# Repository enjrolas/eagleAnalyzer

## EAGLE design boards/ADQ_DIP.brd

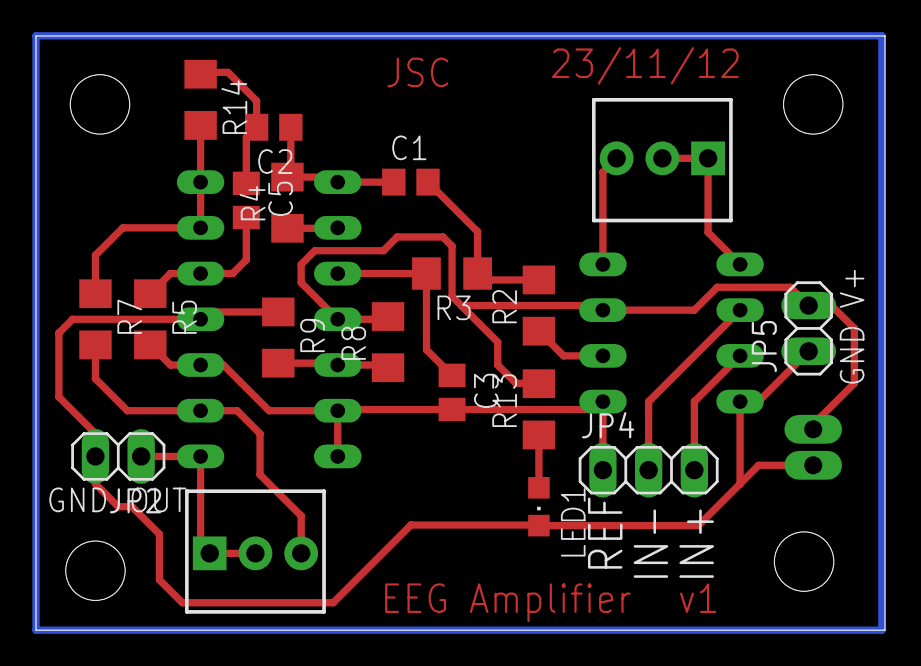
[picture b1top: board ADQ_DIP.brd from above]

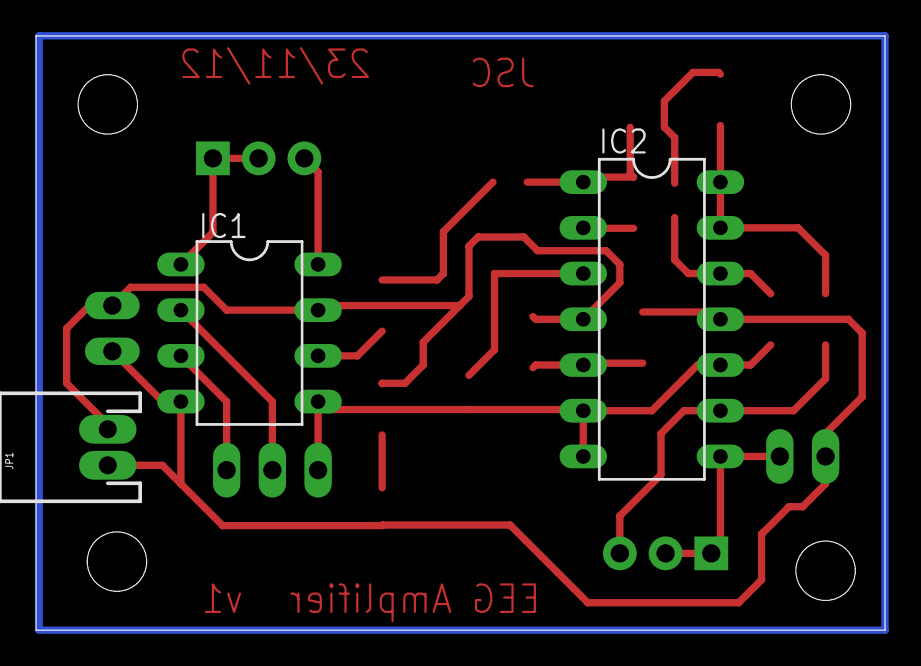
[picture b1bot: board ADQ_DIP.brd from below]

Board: 2 copper layers, 47.2 x 33.0 mm, 26 parts (3 on the bottom side), 19 nets.

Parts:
C1: 220n; C0805
C2, C5: 10u; C0805
C3: 100n; C0805
IC1: AD620N; DIL08
IC2: TL074P; DIL14
JP1: JST-2-PTH
JP2: OUTPUT; 1X02
JP3, JP6, JP7, JP8: STAND-OFF
JP4: INPUT; 1X03
JP5: V+ alt; 1X02
LED1: GREEN; CHIPLED_0805
R1: 500 OHM; 3362U-2
R2, R3: 33k; R1206
R4: 100k; R1206
R5, R8, R9: 51k; R1206
R6: 100k OHM; 3362U-2
R7, R13: 1k; R1206
R14: 22k; R1206

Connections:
GND: IC1.4, IC2.11, JP1.1, JP2.2, JP5.1, LED1.C, R9.1
IN+: IC1.3, JP4.3
IN-: IC1.2, JP4.2
unnamed: IC1.8, R1.3
unnamed: IC1.1, R1.1, R1.2
unnamed: C1.2, R2.2, R3.1
unnamed: IC1.6, R2.1
unnamed: C3.1, IC2.3, R3.2
unnamed: IC2.2, R4.1
unnamed: C1.1, C2.1, IC2.1, R4.2
unnamed: LED1.A, R13.1
unnamed: C2.2, C5.1, R14.1
unnamed: IC2.13, IC2.14, R7.1, R14.2
unnamed: IC2.5, R8.1, R9.2
unnamed: IC2.9, R6.3, R7.2
unnamed: C5.2, IC2.12, R5.1
OUT: IC2.8, JP2.1, R6.1, R6.2
VCC: IC1.7, IC2.4, JP1.2, JP5.2, R8.2, R13.2
VCC/2: C3.2, IC1.5, IC2.6, IC2.7, IC2.10, JP4.1, R5.2

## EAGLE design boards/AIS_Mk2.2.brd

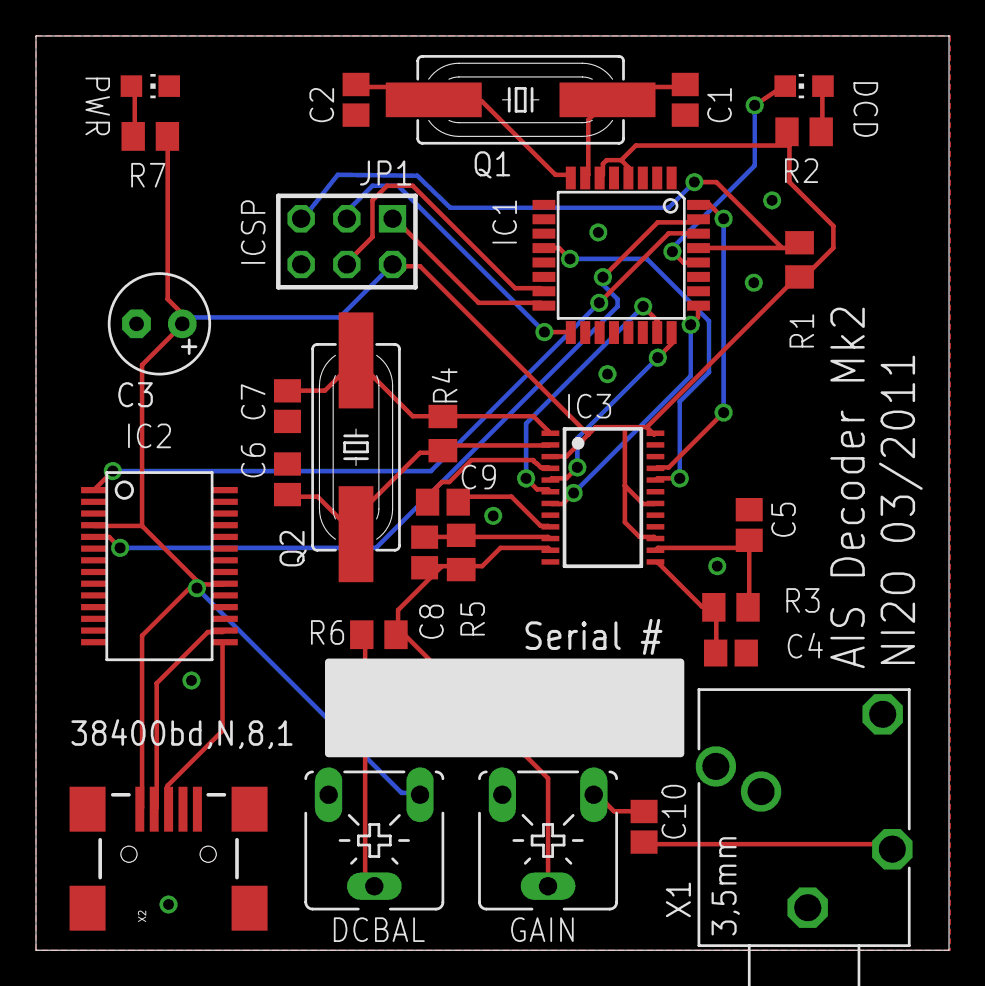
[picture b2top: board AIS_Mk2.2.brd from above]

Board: 2 copper layers, 50.7 x 50.8 mm, 29 parts (0 on the bottom side), 30 nets.

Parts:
C1, C2: 33pF; C0805
C3: 1uF; E2,5-6
C4, C5: 15nF; C0805
C6, C7, C8: 22pF; C0805
C9, C10: 10nF; C0805
DCBAL: 100K; CA6V
GAIN: 100K; CA6V
IC1: MEGA8-AI; TQFP32-08
IC2: FT232RL-BASICSSOP; SSOP28DB
IC3: CMX589AE2; TSSOP24
JP1: AVR-ISP-6
LED1: DATA; CHIP-LED0805
LED2: PWR; CHIP-LED0805
Q1: 8MHz; HC49UP
Q2: 4.9152MHz; HC49UP
R1: 10K; M0805
R2: 470R; M0805
R3, R4: 1M; M0805
R5: 100K; M0805
R6: 270K; M0805
R7: 1K; M0805
X1: PG203J
X2: USBSMD; USB-MINIB

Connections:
+5V: C3.+, DCBAL.A, IC1.4, IC1.6, IC2.4, IC2.20, IC3.3, IC3.15, IC3.18, IC3.24, JP1.2, R1.2, R2.2, R7.1, X2.VBUS
DCBAL: DCBAL.S, R6.1
GND: C1.2, C2.2, C3.-, C4.2, C5.2, C6.2, C7.2, C9.2, DCBAL.E, IC1.3, IC1.5, IC1.21, IC2.7, IC2.18, IC2.21, IC2.25, IC2.26, IC3.4, IC3.8, IC3.12, IC3.17, JP1.6, LED2.C, X1.1, X1.2, X1.3, X2.GND
unnamed: C2.1, IC1.8, Q1.1
unnamed: C1.1, IC1.7, Q1.2
unnamed: IC1.17, JP1.3
unnamed: IC1.16, JP1.1
unnamed: IC1.29, JP1.5, R1.1
unnamed: C4.1, IC3.13, R3.1
unnamed: IC1.28, LED1.C
unnamed: LED1.A, R2.1
unnamed: C5.1, IC3.14, R3.2
unnamed: IC1.30, IC2.1
unnamed: IC1.31, IC2.5
unnamed: C7.1, IC3.1, Q2.1, R4.1
unnamed: C6.1, IC3.2, Q2.2, R4.2
unnamed: C8.1, IC3.10, R5.2
unnamed: C10.2, GAIN.A
unnamed: C10.1, X1.5
unnamed: C9.1, IC3.9
unnamed: IC1.32, IC3.21
unnamed: IC1.12, IC3.20
unnamed: IC1.24, IC3.5
unnamed: IC1.23, IC3.6
unnamed: IC1.25, IC3.7
unnamed: LED2.A, R7.2
unnamed: IC1.15, JP1.4
SIG: C8.2, GAIN.S, IC3.11, R5.1, R6.2
USB+: IC2.15, X2.D+
USB-: IC2.16, X2.D-

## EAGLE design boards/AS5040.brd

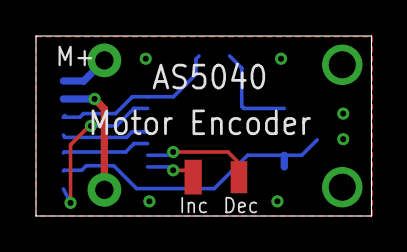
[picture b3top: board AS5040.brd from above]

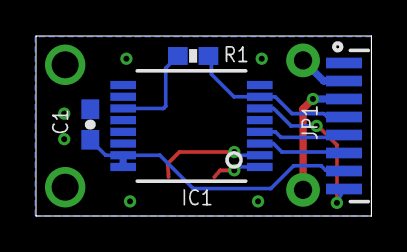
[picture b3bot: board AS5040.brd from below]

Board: 2 copper layers, 18.6 x 10.0 mm, 7 parts (4 on the bottom side), 10 nets.

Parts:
C1: 0603-CAP
IC1: AS5040; SSOP16
JP1: BM08B
JP2: 1X2SMD
JP3, JP5: M01SMDNS; 1X01NS
R1: 0603-RES

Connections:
3.3V: C1.1, IC1.15, IC1.16, JP1.7
CHA: IC1.3, JP1.6
CHB: IC1.4, JP1.5
GND: C1.2, IC1.7, JP1.4, R1.1
INDEX: IC1.6, JP1.8
M1: JP1.3, JP3.1
M2: JP1.2, JP5.1
unnamed: IC1.11, R1.2
unnamed: IC1.1, JP2.P$2
unnamed: IC1.2, JP2.P$1

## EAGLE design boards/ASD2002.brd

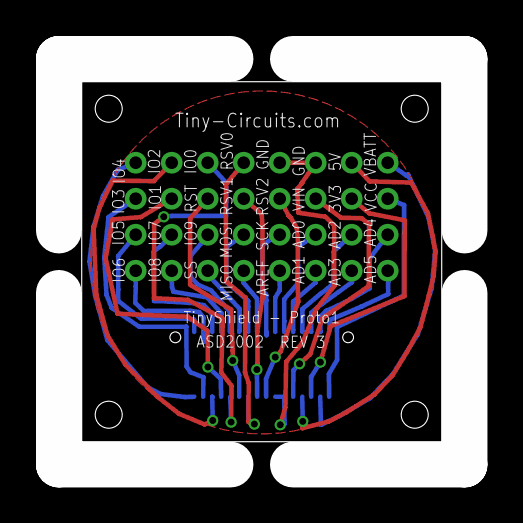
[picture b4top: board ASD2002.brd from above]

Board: 2 copper layers, 20.0 x 20.0 mm, 34 parts (1 on the bottom side), 31 nets.

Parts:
J1: DF12-32-DS
J2, J3, J4, J5, J6, J7, J8, J9, J10, J11, J12, J13, J14, J15, J16, J17, J18, J19, J20, J21, J22, J23, J24, J25, J26, J27, J28, J29, J30, J31, J32, J33: PIN_1X.1"; 1X.1"
U$1: DOCFIELD-TINYCIRCUITS-PCB

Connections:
+3V3: J1.6, J4.1
+5V: J1.8, J5.1
AD0: J1.11, J15.1
AD1: J1.9, J14.1
AD2: J1.7, J13.1
AD3: J1.5, J12.1
AD4/SDA: J1.3, J11.1
AD5/SCL: J1.1, J10.1
AREF: J1.13, J16.1
GND: J1.12, J1.14, J9.1, J33.1
IO0: J1.24, J30.1
IO1: J1.26, J29.1
IO2: J1.28, J28.1
IO3: J1.30, J27.1
IO4: J1.32, J26.1
IO5: J1.31, J25.1
IO6: J1.29, J24.1
IO7: J1.27, J23.1
IO8: J1.25, J22.1
IO9: J1.23, J21.1
MISO: J1.17, J18.1
MOSI: J1.19, J19.1
RESET: J1.22, J31.1
RSV0: J1.20, J17.1
RSV1: J1.18, J8.1
RSV2: J1.16, J7.1
SCK: J1.15, J32.1
SS: J1.21, J20.1
VBATT: J1.4, J3.1
VCC: J1.2, J2.1
VIN: J1.10, J6.1

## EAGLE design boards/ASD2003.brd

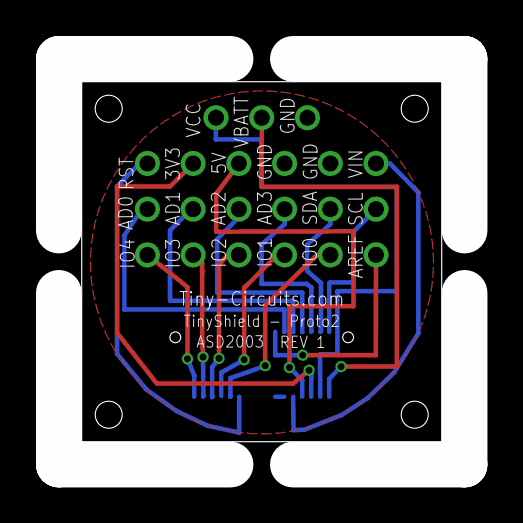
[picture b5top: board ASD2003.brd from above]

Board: 2 copper layers, 20.0 x 20.0 mm, 23 parts (1 on the bottom side), 19 nets.

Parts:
J1, J2, J3, J4, J5, J6, J7, J8, J9, J10, J11, J13, J14, J15, J16, J17, J18, J19, J20, J21, J22: PIN_1X.1"1; 1X.1"_2
J12: DF12-32-DS
U$1: DOCFIELD-TINYCIRCUITS-PCB

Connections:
+3V3: J5.1, J12.6
+5V: J6.1, J12.8
AD0: J10.1, J12.11
AD1: J11.1, J12.9
AD2: J12.7, J13.1
AD3: J12.5, J14.1
AD4/SDA: J12.3, J15.1
AD5/SCL: J12.1, J16.1
AREF: J12.13, J22.1
GND: J3.1, J7.1, J8.1, J12.12, J12.14
IO0: J12.24, J21.1
IO1: J12.26, J20.1
IO2: J12.28, J19.1
IO3: J12.30, J18.1
IO4: J12.32, J17.1
RESET: J4.1, J12.22
VBATT: J2.1, J12.4
VCC: J1.1, J12.2
VIN: J9.1, J12.10

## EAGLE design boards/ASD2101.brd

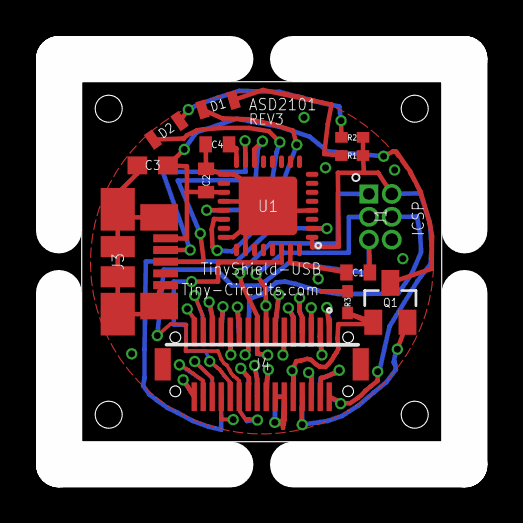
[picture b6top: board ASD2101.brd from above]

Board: 2 copper layers, 20.0 x 20.0 mm, 16 parts (1 on the bottom side), 40 nets.

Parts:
C1, C2, C4: 0.1uF; C0402
C3: 10uF; C0603
D1, D2: AMBER; LNJ_LED
J1: 20021111; 2X3_.05"_TH_HEADER
J2: DF12-32-DS
J3: 47346-0001; MICRO_USB
J4: DF12-32-DP
Q1: DMP2035U; SOT23
R1, R2, R3: 1.00K; 0402
U1: FT232RQ; MLF32
U$1: DOCFIELD-TINYCIRCUITS-PCB

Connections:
+3V3: J2.6, J4.6
+5V: J2.8, J4.8, Q1.2
AD0: J2.11, J4.11
AD1: J2.9, J4.9
AD2: J2.7, J4.7
AD3: J2.5, J4.5
AD4/SDA: J2.3, J4.3
AD5/SCL: J2.1, J4.1
AREF: J2.13, J4.13
DTR: C1.1, U1.31
GND: C2.2, C3.2, C4.2, J1.6, J2.12, J2.14, J3.5, J3.P1, J3.P2, J3.P3, J3.P4, J3.P5, J3.P6, J4.12, J4.14, R3.1, U1.4, U1.17, U1.20, U1.24, U1.26, U1.33
IO0: J2.24, J4.24, U1.30
IO1: J2.26, J4.26, U1.2
IO2: J2.28, J4.28
IO3: J2.30, J4.30
IO4: J2.32, J4.32
IO5: J2.31, J4.31
IO6: J2.29, J4.29
IO7: J2.27, J4.27
IO8: J2.25, J4.25
IO9: J2.23, J4.23
MISO: J1.1, J2.17, J4.17
MOSI: J1.4, J2.19, J4.19
unnamed: C4.1, U1.16
unnamed: J3.2, U1.15
unnamed: D2.C, U1.21
unnamed: D1.A, R1.1
unnamed: D2.A, R2.1
unnamed: J3.3, U1.14
unnamed: D1.C, U1.22
RESET: C1.2, J1.5, J2.22, J4.22
RSV0: J2.20, J4.20
RSV1: J2.18, J4.18
RSV2: J2.16, J4.16
SCK: J1.3, J2.15, J4.15
SS: J2.21, J4.21
USBVCC: C2.1, C3.1, J3.1, Q1.3, U1.19
VBATT: J2.4, J4.4
VCC: J1.2, J2.2, J4.2, R1.2, R2.2, U1.1
VIN: J2.10, J4.10, Q1.1, R3.2

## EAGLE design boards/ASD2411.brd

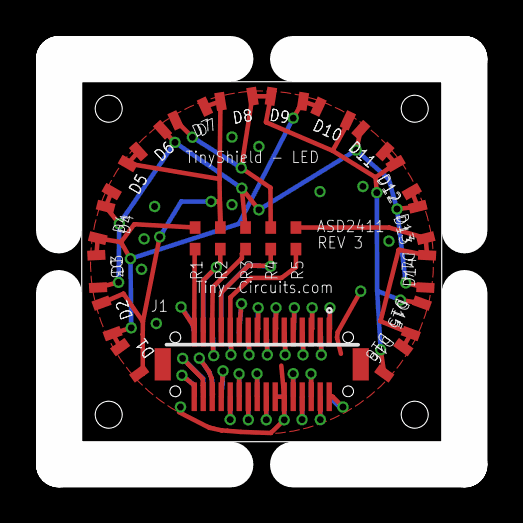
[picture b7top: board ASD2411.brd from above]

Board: 2 copper layers, 20.0 x 20.0 mm, 24 parts (1 on the bottom side), 36 nets.

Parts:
D1, D2, D3, D4, D5, D6, D7, D8, D9, D10, D11, D12, D13, D14, D15, D16: GREEN; LNJ_LED
J1: DF12-32-DP
J2: DF12-32-DS
R1, R2, R3, R4, R5: 300; 0402
U$1: DOCFIELD-TINYCIRCUITS-PCB

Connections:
+3V3: J1.6, J2.6
+5V: J1.8, J2.8
AD0: J1.11, J2.11
AD1: J1.9, J2.9
AD2: J1.7, J2.7
AD3: J1.5, J2.5
AD4/SDA: J1.3, J2.3
AD5/SCL: J1.1, J2.1
AREF: J1.13, J2.13
GND: J1.12, J1.14, J2.12, J2.14
IO0: J1.24, J2.24
IO1: J1.26, J2.26
IO2: J1.28, J2.28
IO3: J1.30, J2.30
IO4: J1.32, J2.32
IO5: J1.31, J2.31, R1.2
IO6: J1.29, J2.29, R2.2
IO7: J1.27, J2.27, R3.2
IO8: J1.25, J2.25, R4.2
IO9: J1.23, J2.23, R5.2
MISO: J1.17, J2.17
MOSI: J1.19, J2.19
unnamed: D1.C, D2.A, D5.A, D6.C, D7.A, D8.C, R2.1
unnamed: D1.A, D2.C, D3.A, D4.C, D9.A, D10.C, R1.1
unnamed: D3.C, D4.A, D5.C, D6.A, D11.C, D12.A, D13.C, D14.A, R3.1
unnamed: D7.C, D8.A, D9.C, D10.A, D11.A, D12.C, D15.C, D16.A, R4.1
unnamed: D13.A, D14.C, D15.A, D16.C, R5.1
RESET: J1.22, J2.22
RSV0: J1.20, J2.20
RSV1: J1.18, J2.18
RSV2: J1.16, J2.16
SCK: J1.15, J2.15
SS: J1.21, J2.21
VBATT: J1.4, J2.4
VCC: J1.2, J2.2
VIN: J1.10, J2.10

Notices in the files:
boards/ASD2002.brd:
Released under the Creative Commons Attribution Share-Alike 3.0 License
http://creativecommons.org/licenses/by-sa/3.0
parts and their libraries:
SparkFun: Licensing: CC v3.0 Share-Alike You are welcome to use this library for commercial purposes.
